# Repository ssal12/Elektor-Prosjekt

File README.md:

# Elektor-Prosjekt
Prosjekt archive til prosjektet som ble gjennomført i emnet IELEG2113 på NTNU Gjøvik høsten 2025.

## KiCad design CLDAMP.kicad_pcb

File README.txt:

README – PCB Design Notes
————————————

The PCB layouts provided in this project are intended as educational prototypes and reference material. They were designed by students and, while they adhere to basic design rules (clearances, trace widths, two-layer routing with ground reference planes, mounting holes, etc.), they haven’t been reviewed or optimized by a professional PCB designer. Therefore, any reuse in a demanding application should involve a thorough redesign.

Board-specific comments
———————————

1. Microphone Preamplifier PCB

- This is the most refined of the three boards.
- The board is compact, with short signal paths between the input connector, the JFET bias network, the THAT1512 preamplifier, and the output connector.
- The routing is relatively clean and direct; analogue signal traces are separated from the DC-DC converter section, and decoupling capacitors are placed close to the NMA0515SC converter and the preamp IC.
- A largely continuous bottom-layer ground plane is used, with local pours around the supply section.
- Further improvements are possible (e.g., more explicit star-grounding at the input, additional shielding around high-impedance nodes), but this layout serves as a reasonable starting point for a low-noise preamp.

2. Single-Supply Class-D Amplifier PCB

- This board represents an intermediate level of quality between the preamp and the dual-supply amplifier.
- The high-current path from the supply connector, through the bulk capacitors, MOSFETs, and output inductor is routed with reasonably wide traces and kept on the upper half of the board. A vertical “VCC spine” along the left side distributes the supply to the power stage.
- The modulator (555, LM393, and associated components) is placed toward the lower edge, with shorter local traces but less shielding from the power section than would be ideal in a production design.
   - Copper pours are used sparingly; most return currents flow in a largely unbroken bottom-layer ground region.

For further iterations, the layout could benefit from tighter current loops around the half-bridge and output filter, clearer separation between power and small-signal areas, and more systematic stitching between the top traces and the ground plane.

3. Dual-Supply Class-D Amplifier PCB

- The dual-supply (bipolar) amplifier PCB is functionally complete but the least tidy of the three designs.

- Wide copper pours and broad traces are extensively used on the top layer to distribute both +V and –V rails from the fuse/connector area to the half-bridge and output filter. This provides low DC resistance but results in irregular current paths and large copper “islands” that are not always well-controlled.

- The central power stage and the lower-right modulator/driver section are relatively dense, with several long signal traces weaving through power copper. This is acceptable for a lab prototype but would be sub-optimal for EMI and reproducibility in a production context.

- The bottom layer is predominantly a ground/reference plane, but in some regions it is cut up by numerous vias and pours, which can fragment return paths.

- A future revision should rationalize the power distribution (clear, short high-current loops; well-defined star points), reduce unnecessary copper, and more clearly isolate the analogue/PWM circuitry from the high-di/dt switching node.

Summary
———

Overall, the PCBs are suitable for demonstrating the concepts discussed in the report and for laboratory prototyping, but they should not be regarded as optimized or production-ready layouts. Anyone reusing these designs is strongly encouraged to treat them as first-pass examples and to perform a full layout review and at least one additional revision cycle before deploying them in a more demanding setting.

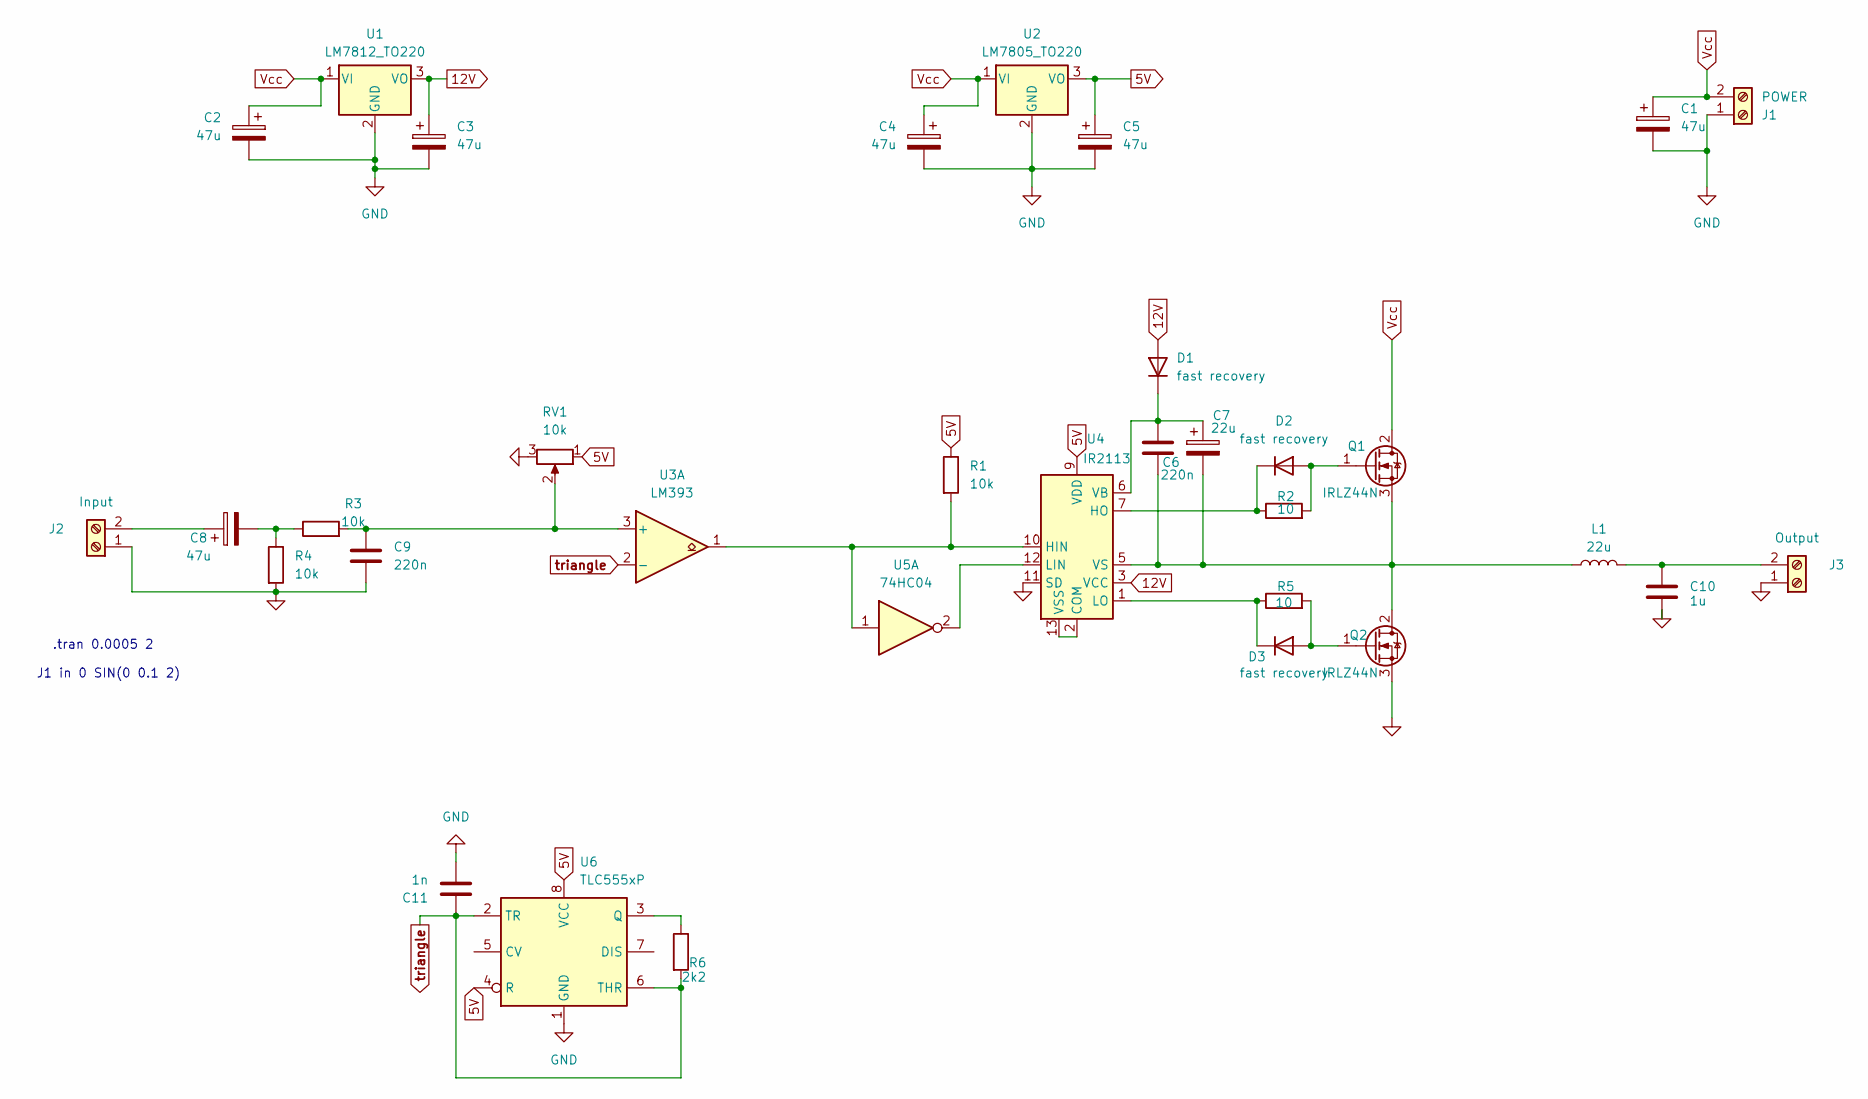
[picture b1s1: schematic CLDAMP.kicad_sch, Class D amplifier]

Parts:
C1, C2, C3, C4, C5, C8: 47u; CP_Radial_D10.0mm_P5.00mm
C6, C9: 220n; C_Rect_L10.0mm_W4.0mm_P7.50mm_FKS3_FKP3
C7: 22u; C_Radial_D6.3mm_H11.0mm_P2.50mm
C10: 1u; C_Rect_L18.0mm_W9.0mm_P15.00mm_FKS3_FKP3
C11: 1n; C_Disc_D3.4mm_W2.1mm_P2.50mm
D1, D2, D3: fast recovery; D_DO-41_SOD81_P10.16mm_Horizontal
J1: POWER; TerminalBlock_Phoenix_MKDS-1,5-2-5.08_1x02_P5.08mm_Horizont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
J2: Input; TerminalBlock_Phoenix_MKDS-1,5-2-5.08_1x02_P5.08mm_Horizont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
J3: Output; TerminalBlock_Phoenix_MKDS-1,5-2-5.08_1x02_P5.08mm_Horizont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
L1: 22u; L_Toroid_Vertical_L33.0mm_W17.8mm_P12.70mm_Pulse_KM-5
Q1, Q2: IRLZ44N; TO-220-3_Vertical
R1, R4: 10k; R_Axial_DIN0207_L6.3mm_D2.5mm_P10.16mm_Horizontal
R2, R5: 10; R_Axial_DIN0207_L6.3mm_D2.5mm_P10.16mm_Horizontal
R3: 10k; R_Axial_DIN0309_L9.0mm_D3.2mm_P5.08mm_Vertical
R6: 2k2; R_Axial_DIN0309_L9.0mm_D3.2mm_P5.08mm_Vertical
RV1: 10k; Potentiometer_Bourns_3299P_Horizontal
U1: LM7812_TO220; TO-220-3_Vertical
U2: LM7805_TO220; TO-220-3_Vertical
U3: LM393; DIP-8_W7.62mm_Socket
U4: IR2113; DIP-14_W7.62mm_Socket
U5: 74HC04; DIP-14_W7.62mm_Socket
U6: TLC555xP; DIP-8_W7.62mm_Socket

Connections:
5V: C5.1, R1.1, RV1.1, U2.3 (VO), U4.9 (VDD), U6.4 (R), U6.8 (VCC)
12V: C3.1, D1.2 (A), U1.3 (VO), U4.3 (VCC)
GND: C1.2, C2.2, C3.2, C4.2, C5.2, C9.2, C10.2, C11.2, J1.1, J2.1, J3.1, Q2.3 (S), R4.2, RV1.3, U1.2 (GND), U2.2 (GND), U4.11 (SD), U6.1 (GND)
unnamed: C8.2, R3.1, R4.1
unnamed: C6.1, C7.1, D1.1 (K), U4.6 (VB)
unnamed: D2.2 (A), Q1.1 (G), R2.2
unnamed: D2.1 (K), R2.1, U4.7 (HO)
unnamed: D3.2 (A), Q2.1 (G), R5.2
unnamed: D3.1 (K), R5.1, U4.1 (LO)
unnamed: C8.1, J2.2
unnamed: C10.1, J3.2, L1.2
unnamed: C6.2, C7.2, L1.1, Q1.3 (S), Q2.2 (D), U4.5 (VS)
unnamed: C9.1, R3.2, RV1.2, U3.3 (+)
unnamed: U4.2 (COM), U4.13 (VSS)
unnamed: R1.2, U3.1, U4.10 (HIN), U5.1
unnamed: U4.12 (LIN), U5.2
unnamed: R6.1, U6.3 (Q)
Vcc: C1.1, C2.1, C4.1, J1.2, Q1.2 (D), U1.1 (VI), U2.1 (VI)
triangle: C11.1, R6.2, U3.2 (-), U6.2 (TR), U6.6 (THR)

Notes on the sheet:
.tran 0.0005 2
J1 in 0 SIN(0 0.1 2)

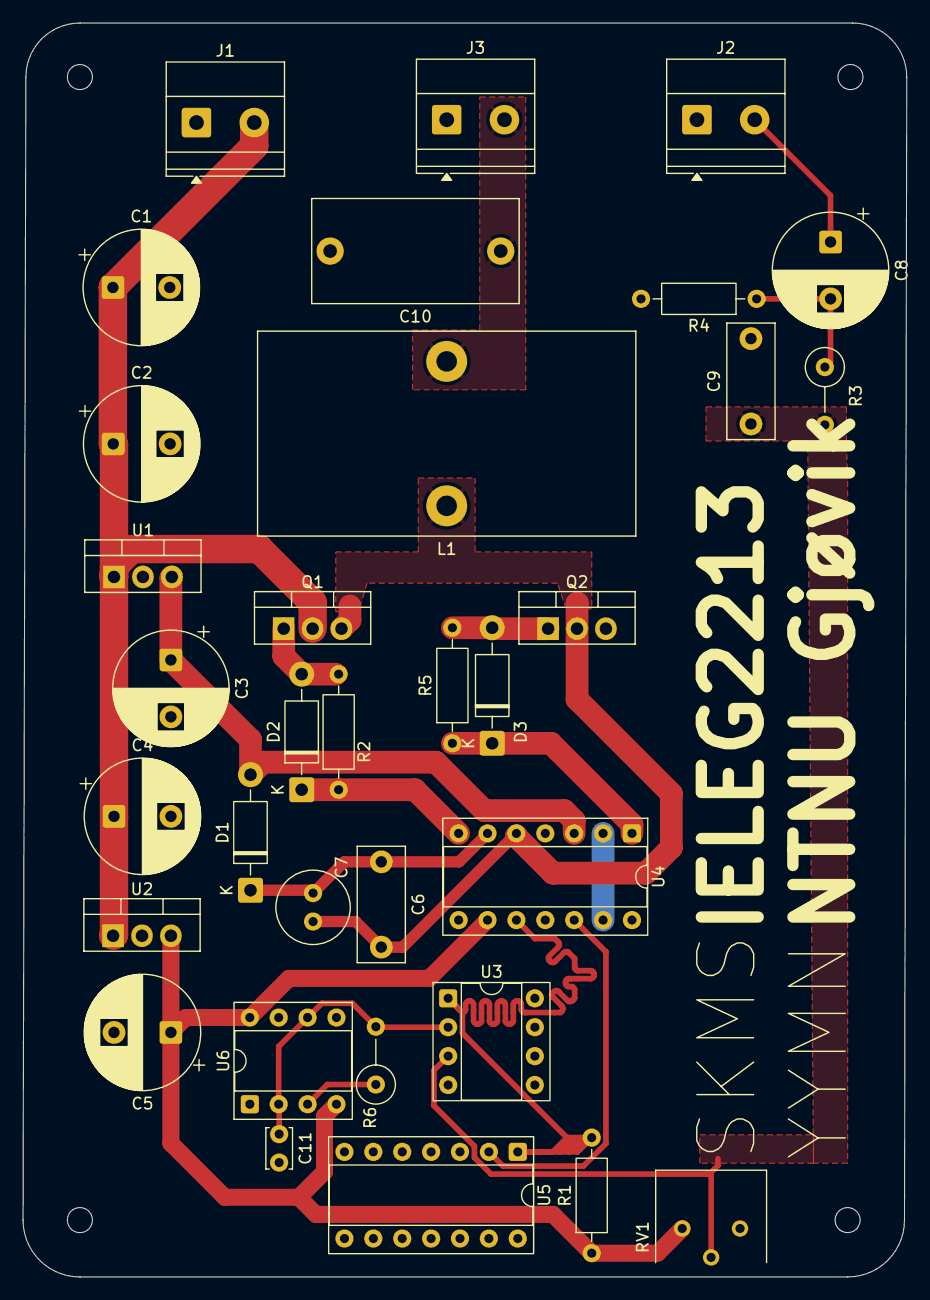
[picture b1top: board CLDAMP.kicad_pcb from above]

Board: 2 copper layers, 77.7 x 110.2 mm, 37 parts (0 on the bottom side), 19 nets.

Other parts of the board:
H1, H2, H3, H4: MountingHole; MountingHole_2.2mm_M2

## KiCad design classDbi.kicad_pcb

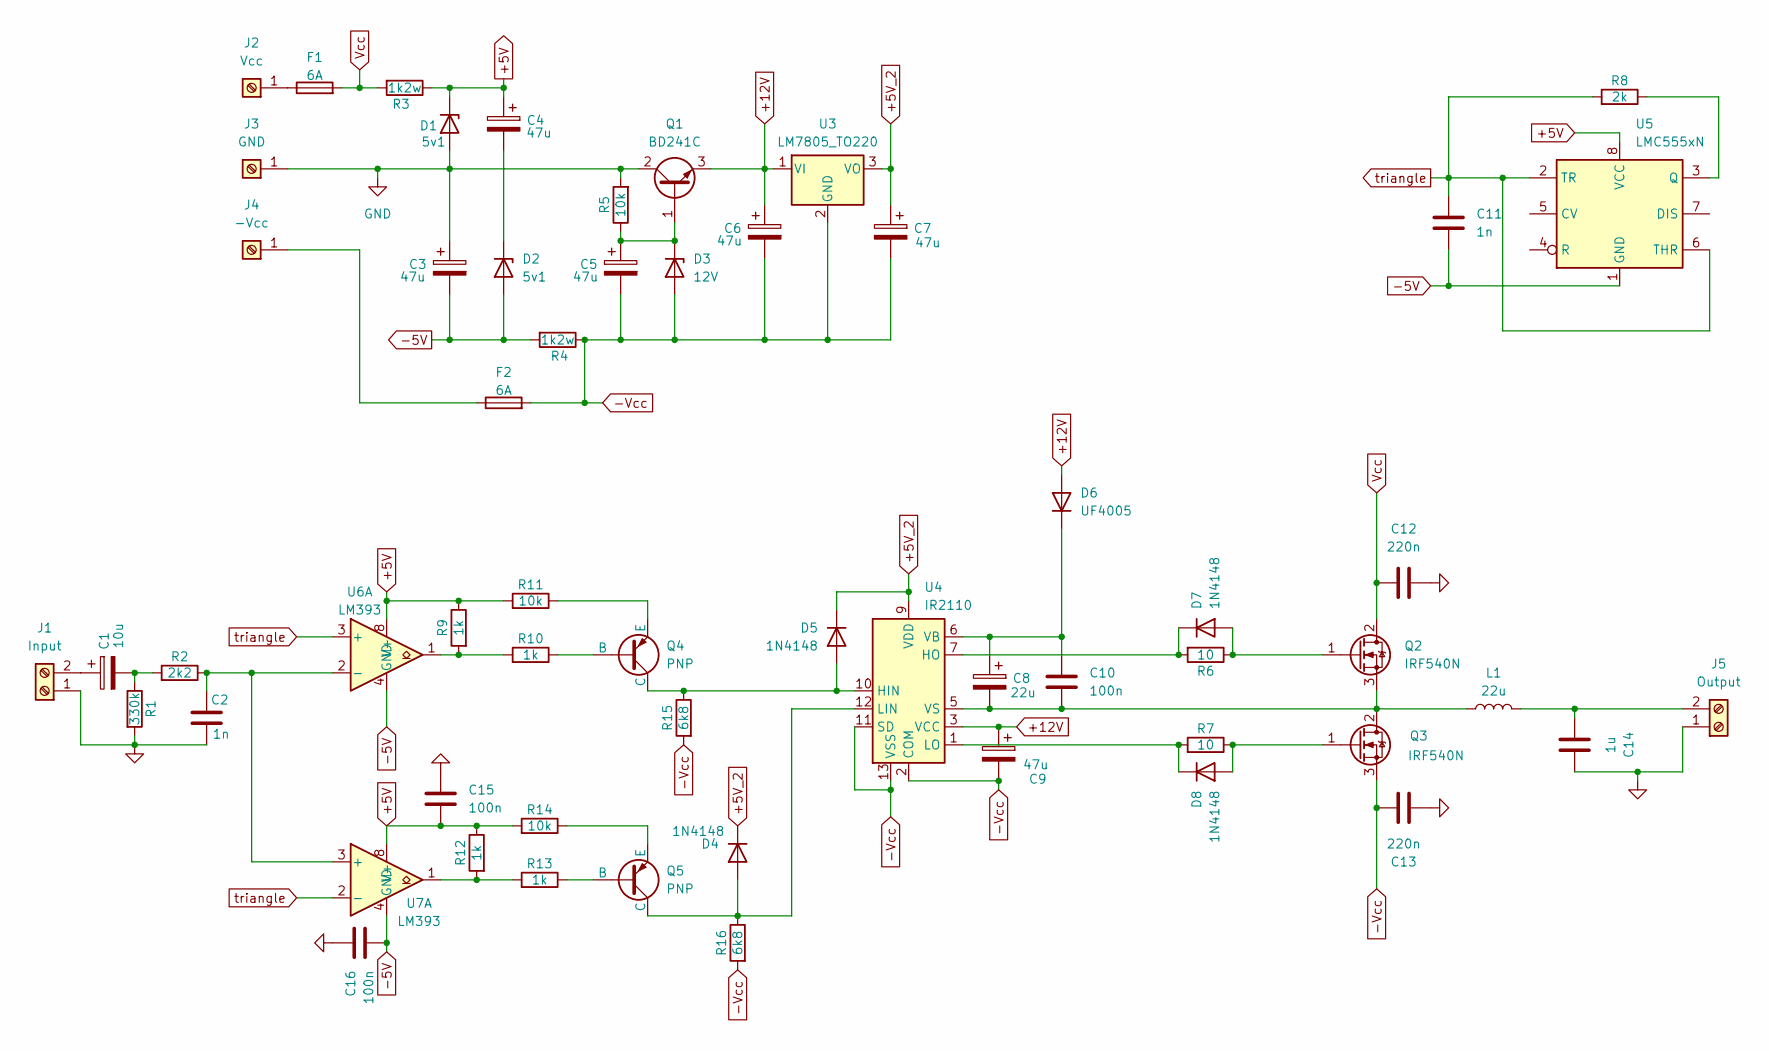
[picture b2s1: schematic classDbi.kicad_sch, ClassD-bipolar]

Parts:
C1: 10u; CP_Radial_D5.0mm_P2.50mm
C2: 1n; C_Rect_L4.0mm_W2.5mm_P2.50mm
C3, C4, C5, C6, C7, C9: 47u; CP_Radial_D8.0mm_P2.50mm
C8: 22u; CP_Radial_D6.3mm_P2.50mm
C10, C15, C16: 100n; C_Rect_L7.0mm_W2.5mm_P5.00mm
C11: 1n; C_Disc_D4.3mm_W1.9mm_P5.00mm
C12, C13: 220n; C_Rect_L9.0mm_W3.2mm_P7.50mm_MKT
C14: 1u; C_Rect_L19.0mm_W11.0mm_P15.00mm_MKS4
D1, D2: 5v1; D_DO-34_SOD68_P7.62mm_Horizontal
D3: 12V; D_DO-34_SOD68_P7.62mm_Horizontal
D4, D5, D7, D8: 1N4148; D_DO-35_SOD27_P7.62mm_Horizontal
D6: UF4005; D_DO-35_SOD27_P7.62mm_Horizontal
F1, F2: 6A; Fuseholder_Cylinder-5x20mm_Schurter_0031_8201_Horizontal_Op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
J1: Input; TerminalBlock_Phoenix_MKDS-1,5-2-5.08_1x02_P5.08mm_Horizont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
J2: Vcc; TerminalBlock_Phoenix_MKDS-1,5-2-5.08_1x02_P5.08mm_Horizont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
J3: GND; TerminalBlock_Phoenix_MKDS-1,5-2-5.08_1x02_P5.08mm_Horizont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
J4: -Vcc; TerminalBlock_Phoenix_MKDS-1,5-2-5.08_1x02_P5.08mm_Horizont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
J5: Output; TerminalBlock_Phoenix_MKDS-1,5-2-5.08_1x02_P5.08mm_Horizont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
L1: 22u; L_Toroid_Vertical_L33.0mm_W17.8mm_P12.70mm_Pulse_KM-5
Q1: BD241C; TO-220-3_Vertical
Q2, Q3: IRF540N; TO-220-3_Vertical
Q4, Q5: PNP; TO-92
R1: 330k; R_Axial_DIN0207_L6.3mm_D2.5mm_P10.16mm_Horizontal
R2: 2k2; R_Axial_DIN0207_L6.3mm_D2.5mm_P10.16mm_Horizontal
R3, R4: 1k2w; R_Axial_DIN0309_L9.0mm_D3.2mm_P5.08mm_Vertical
R5, R11, R14: 10k; R_Axial_DIN0207_L6.3mm_D2.5mm_P10.16mm_Horizontal
R6, R7: 10; R_Axial_DIN0207_L6.3mm_D2.5mm_P10.16mm_Horizontal
R8: 2k; R_Axial_DIN0309_L9.0mm_D3.2mm_P2.54mm_Vertical
R9, R10, R12, R13: 1k; R_Axial_DIN0207_L6.3mm_D2.5mm_P10.16mm_Horizontal
R15, R16: 6k8; R_Axial_DIN0207_L6.3mm_D2.5mm_P10.16mm_Horizontal
U3: LM7805_TO220; TO-220-3_Vertical
U4: IR2110; DIP-14_W7.62mm_Socket
U5: LMC555xN; DIP-8_W7.62mm_Socket
U6, U7: LM393; DIP-8_W7.62mm_Socket

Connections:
+5V: C4.1, C15.2, D1.1 (K), R3.1, R9.1, R11.2, R12.1, R14.2, U5.8 (VCC), U6.8 (V+), U7.8 (V+)
+5V_2: C7.1, D4.1 (K), D5.1 (K), U3.3 (VO), U4.9 (VDD)
+12V: C6.1, C9.1, D6.2 (A), Q1.3 (E), U3.1 (VI), U4.3 (VCC)
-5V: C3.2, C11.2, C16.2, D2.2 (A), R4.2, U5.1 (GND), U6.4 (GND), U7.4 (GND)
-Vcc: C5.2, C6.2, C7.2, C9.2, C13.1, D3.2 (A), F2.2, Q3.3 (S), R4.1, R15.2, R16.2, U3.2 (GND), U4.2 (COM), U4.11 (SD), U4.13 (VSS)
GND: C2.2, C3.1, C12.2, C13.2, C14.1, C15.1, C16.1, D1.2 (A), J1.1, J3.1, J3.2, J5.1, Q1.2 (C), R1.2, R5.2
unnamed: C1.2, R1.1, R2.2
unnamed: C4.2, D2.1 (K)
unnamed: C5.1, D3.1 (K), Q1.1 (B), R5.1
unnamed: D4.2 (A), Q5.1 (C), R16.1, U4.12 (LIN)
unnamed: D5.2 (A), Q4.1 (C), R15.1, U4.10 (HIN)
unnamed: C8.1, C10.1, D6.1 (K), U4.6 (VB)
unnamed: D7.2 (A), Q2.1 (G), R6.1
unnamed: D7.1 (K), R6.2, U4.7 (HO)
unnamed: D8.2 (A), Q3.1 (G), R7.1
unnamed: D8.1 (K), R7.2, U4.1 (LO)
unnamed: C1.1, J1.2
unnamed: F1.1, J2.1, J2.2
unnamed: F2.1, J4.1, J4.2
unnamed: C14.2, J5.2, L1.2
unnamed: C8.2, C10.2, L1.1, Q2.3 (S), Q3.2 (D), U4.5 (VS)
unnamed: Q4.2 (B), R10.1
unnamed: Q4.3 (E), R11.1
unnamed: Q5.2 (B), R13.1
unnamed: Q5.3 (E), R14.1
unnamed: R9.2, R10.2, U6.1
unnamed: R12.2, R13.2, U7.1
unnamed: R8.1, U5.3 (Q)
unnamed: C2.1, R2.1, U6.2 (-), U7.3 (+)
Vcc: C12.1, F1.2, Q2.2 (D), R3.2
triangle: C11.1, R8.2, U5.2 (TR), U5.6 (THR), U6.3 (+), U7.2 (-)

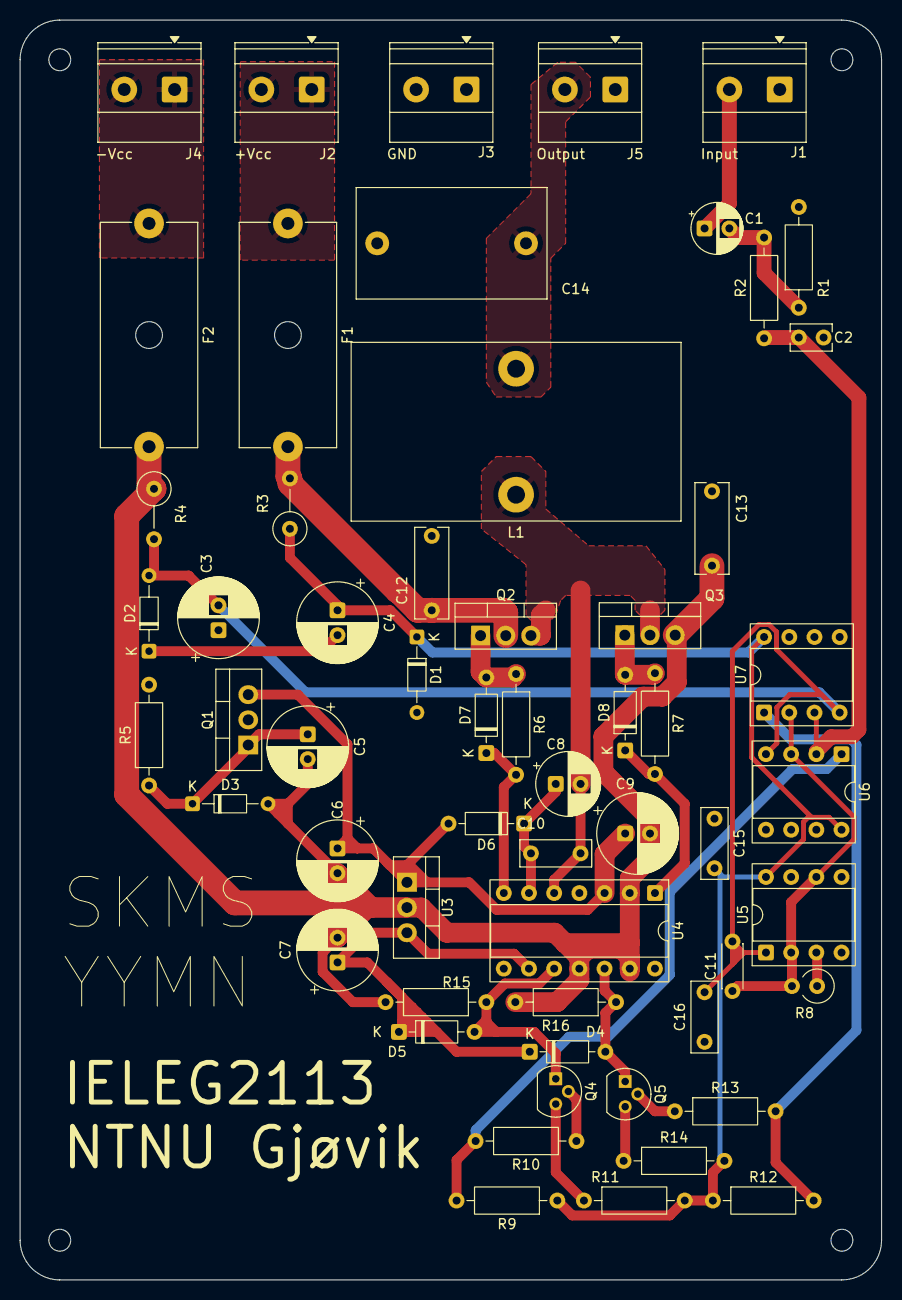
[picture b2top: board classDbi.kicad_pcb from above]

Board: 2 copper layers, 86.8 x 127.0 mm, 58 parts (0 on the bottom side), 31 nets.
